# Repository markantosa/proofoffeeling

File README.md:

# Proof of Feeling

**Affective Core AC-7** — a speculative mechatronic artefact: an artificial
robotic heart that makes a humanoid AI's internal state visible through
pulse, motion, and light.

<p align="center">
  
  <br><sub>Render made in Blender.</sub>
</p>

<p align="center">
  
  <br><sub>▶ Short demo — <a href="https://youtu.be/jkcCoCJa7ys">watch on YouTube</a></sub>
</p>

See [`docs/design-reference.md`](docs/design-reference.md) for the full
project concept and design brief.

## Repository Layout

```
.
├── docs/               Project-wide documentation
│   ├── design-reference.md          Project context/story + physical prototype
│   └── pcb-design-reference.md      KiCad 10 PCB design reference
├── firmware/           ESP32-C6-Supermini embedded firmware
│   ├── src/             Servo sweep, LED chase, proximity speed, eye animation, BLE telemetry
│   └── include/          Pin assignments, tunables, BLE UUIDs
├── dashboard/          BLE debug dashboard — ASCII face/sonar/heartbeat, Web Bluetooth (Chrome/Edge only)
├── electronics/        KiCad PCB project (single-layer milled board)
└── mechanical/         3D models — printable STL/3MF tracked via Git LFS; source .blend files not included yet
```

## Hardware Summary

* ESP32-C6-Supermini
* 2x SG92R micro servos, 5V (continuous 0–180° sweep, mirrored) — chosen over MG995 for size
* HC-SR04 ultrasonic sensor (proximity → continuous speed control)
* 1x momentary button, wired but currently unused by firmware
* 8x auxiliary LEDs, top-to-bottom chase ("pulse point" glow array)
* I2C OLED (SSD1306-class), 4-pin header — always-on blinking eye
* BLE telemetry (built-in radio) — feeds the debug dashboard, see below
* Custom single-layer milled PCB (KiCad, `electronics/`)
* Powered via 5V DC barrel plug

## Tools

* 3D modelling — Blender
* PCB design — KiCad
* Firmware — written with the aid of Claude

## Credits

* Heart geometry developed from [Realistic Human Heart](https://sketchfab.com/3d-models/realistic-human-heart-3f8072336ce94d18b3d0d055a1ece089) (Sketchfab)

<table>
  <tr>
    <td align="center"><br><sub>Populated board render</sub></td>
    <td align="center"><br><sub>B.Cu routing</sub></td>
    <td align="center"><br><sub>Desktop CNC isolation milling</sub></td>
  </tr>
</table>

## Build

<table>
  <tr>
    <td align="center"><br><sub>Assembly</sub></td>
    <td align="center"><br><sub>Finished artefact</sub></td>
  </tr>
</table>

## Getting Started

* Project context, story, and what a viewer experiences: [`docs/design-reference.md`](docs/design-reference.md)
* Firmware build/flash instructions: [`firmware/README.md`](firmware/README.md)
* PCB design reference: [`docs/pcb-design-reference.md`](docs/pcb-design-reference.md)
* KiCad project: [`electronics/EPD 3D G6.kicad_pro`](electronics/EPD%203D%20G6.kicad_pro)
* BLE debug dashboard: [`dashboard/index.html`](dashboard/index.html) — open directly in Chrome or Edge (desktop/Android; Web Bluetooth isn't supported in Firefox/Safari), click **Connect**, pick "AC-7"

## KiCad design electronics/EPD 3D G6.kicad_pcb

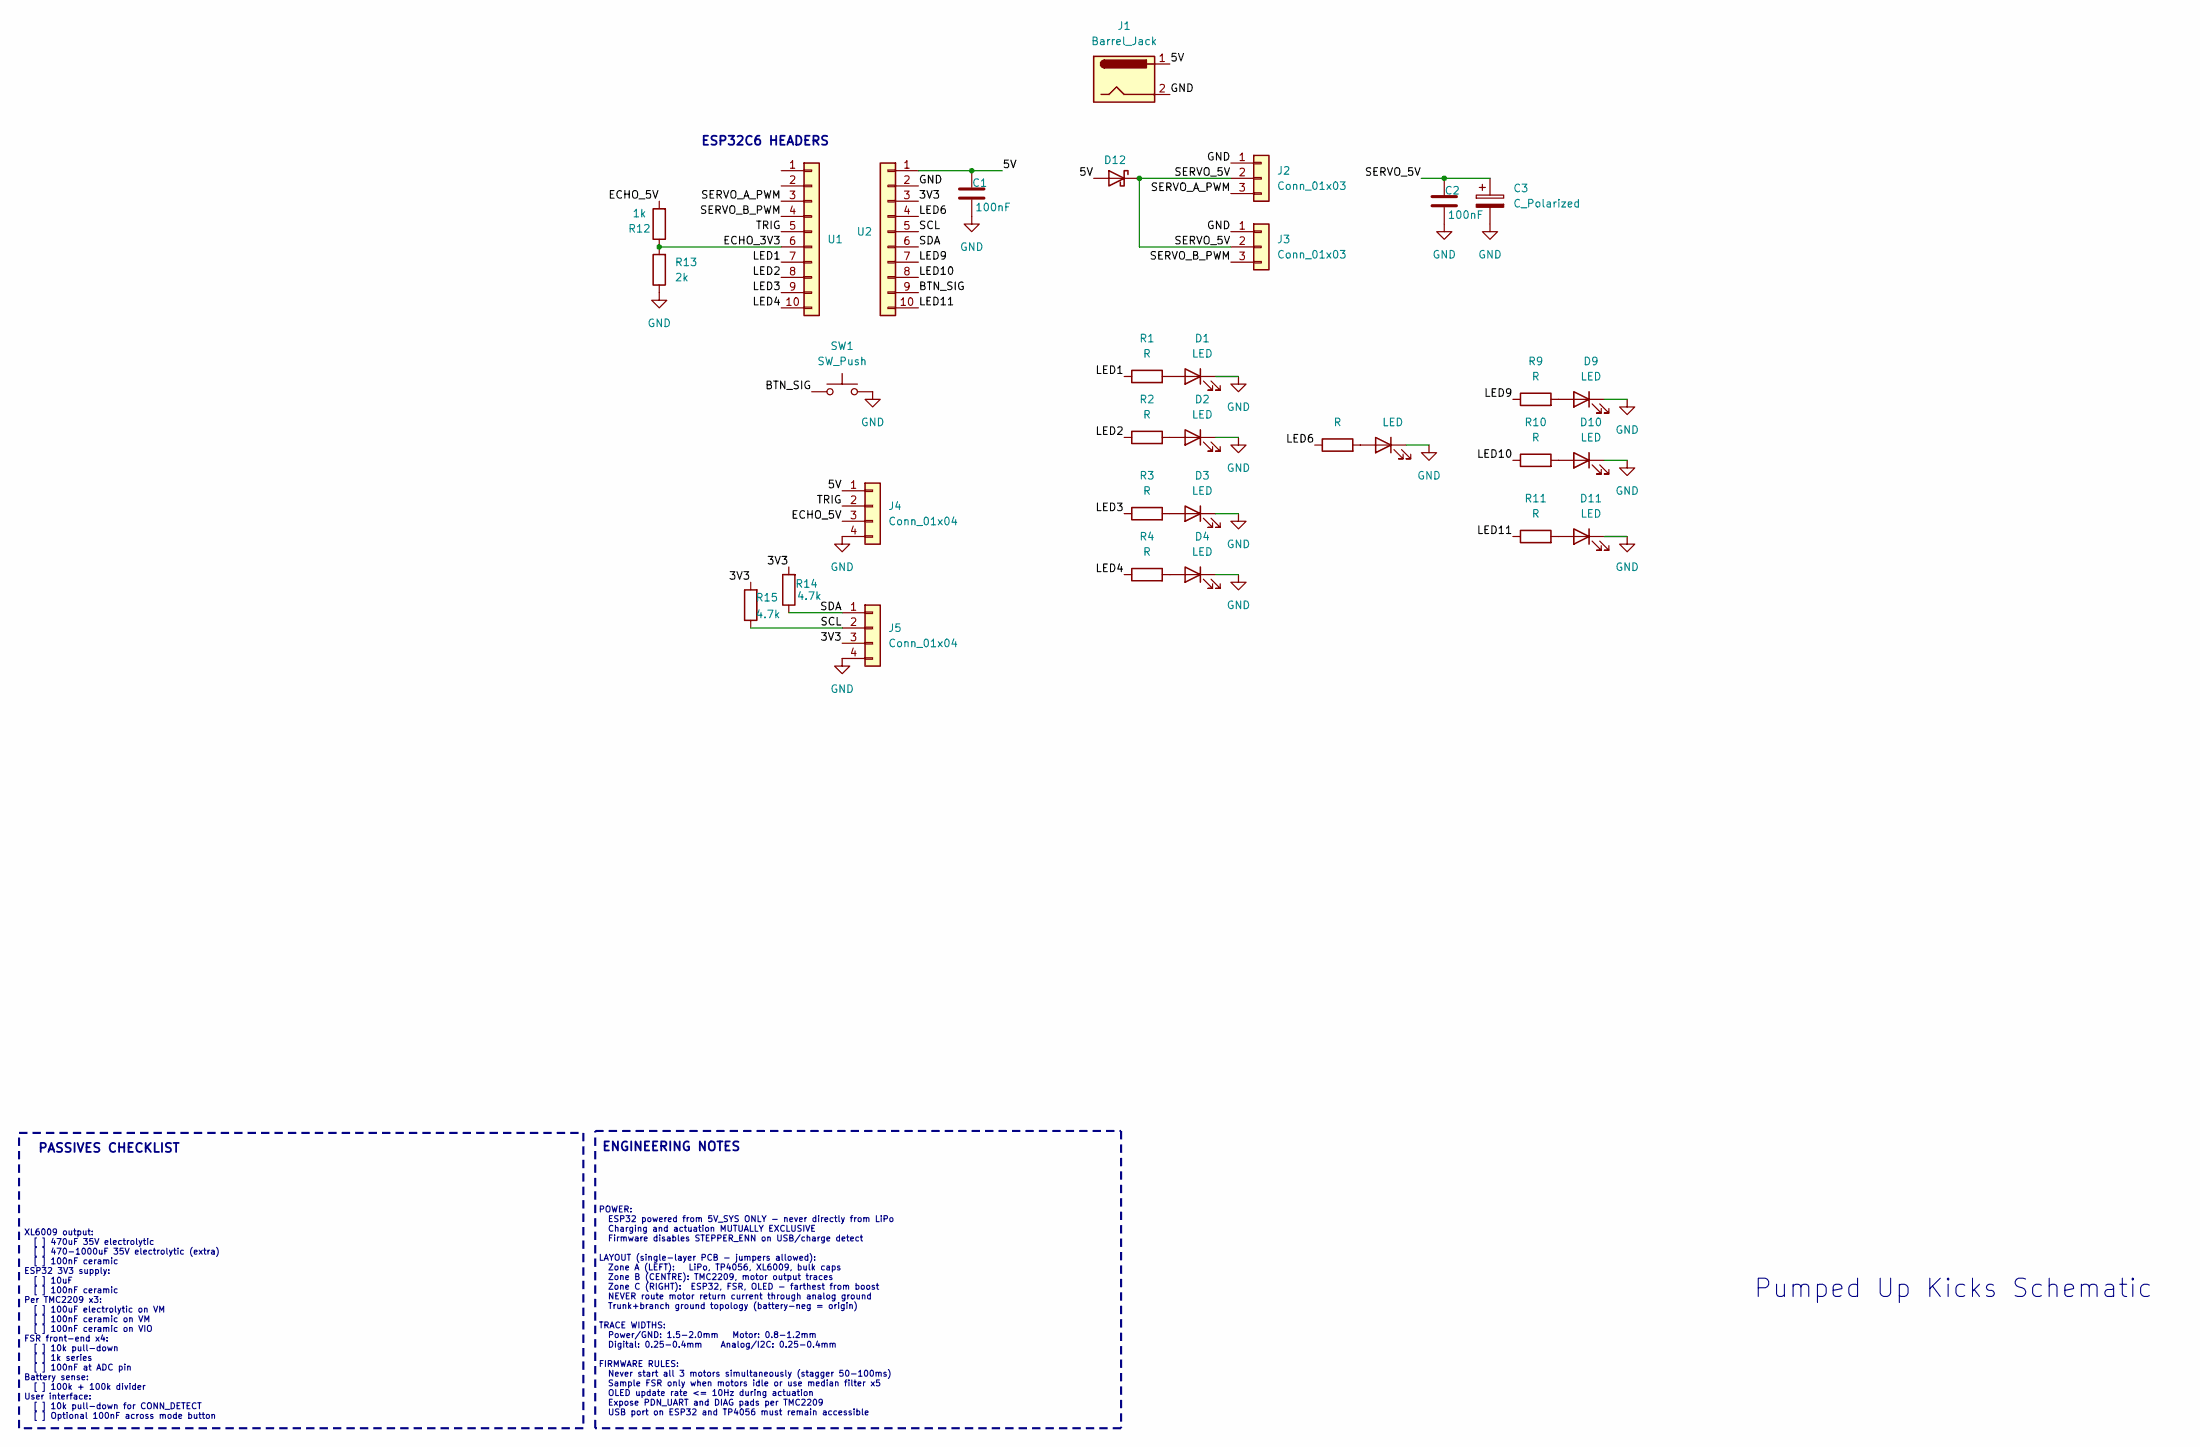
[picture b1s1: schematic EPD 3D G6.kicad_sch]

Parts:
C1, C2: 100nF; C_Disc_D5.0mm_W2.5mm_P5.00mm
C3: C_Polarized; CP_Radial_D8.0mm_P3.50mm
D1, D2, D3, D4, D6, D9, D10, D11: LED; LED_D5.0mm
D12: D_Schottky; D_DO-201AD_P15.24mm_Horizontal
J1: Barrel_Jack; BarrelJack_GCT_DCJ200-10-A_Horizontal
J2, J3: Conn_01x03; PinSocket_1x03_P2.54mm_Vertical
J4, J5: Conn_01x04; PinSocket_1x04_P2.54mm_Vertical
R1, R2, R3, R4, R6, R9, R10, R11: R; R_Axial_DIN0207_L6.3mm_D2.5mm_P7.62mm_Horizontal
R12: 1k; R_Axial_DIN0207_L6.3mm_D2.5mm_P7.62mm_Horizontal
R13: 2k; R_Axial_DIN0207_L6.3mm_D2.5mm_P7.62mm_Horizontal
R14, R15: 4.7k; R_Axial_DIN0207_L6.3mm_D2.5mm_P7.62mm_Horizontal
SW1: SW_Push; SW_PUSH_6mm
U1, U2: Conn_01x10; PinSocket_1x10_P2.54mm_Vertical

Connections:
/3V3: J5.3, R14.2, R15.2, U2.3
/5V: C1.1, D12.2 (A), J1.1, J4.1, U2.1
/BTN_SIG: SW1.1, U2.9
/ECHO_3V3: R12.1, R13.2, U1.6
/ECHO_5V: J4.3, R12.2
/LED1: R1.1, U1.7
/LED2: R2.1, U1.8
/LED3: R3.1, U1.9
/LED4: R4.1, U1.10
/LED6: R6.1, U2.4
/LED9: R9.1, U2.7
/LED10: R10.1, U2.8
/LED11: R11.1, U2.10
/SCL: J5.2, R15.1, U2.5
/SDA: J5.1, R14.1, U2.6
/SERVO_5V: C2.1, C3.1, D12.1 (K), J2.2, J3.2
/SERVO_A_PWM: J2.3, U1.3
/SERVO_B_PWM: J3.3, U1.4
/TRIG: J4.2, U1.5
GND: C1.2, C2.2, C3.2, D1.1 (K), D2.1 (K), D3.1 (K), D4.1 (K), D6.1 (K), D9.1 (K), D10.1 (K), D11.1 (K), J1.2, J2.1, J3.1, J4.4, J5.4, R13.1, SW1.2, U2.2
unnamed: D1.2 (A), R1.2
unnamed: D2.2 (A), R2.2
unnamed: D3.2 (A), R3.2
unnamed: D4.2 (A), R4.2
unnamed: D6.2 (A), R6.2
unnamed: D9.2 (A), R9.2
unnamed: D10.2 (A), R10.2
unnamed: D11.2 (A), R11.2

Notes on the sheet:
Pumped Up Kicks Schematic
PASSIVES CHECKLIST
ESP32C6 HEADERS
XL6009 output: [ ] 470uF 35V electrolytic [ ] 470-1000uF 35V electrolytic (extra) [ ] 100nF ceramic ESP32 3V3 supply: [ ] 10uF [ ] 100nF ceramic Per TMC2209 x3: [ ] 100uF electrolytic on VM [ ] 100nF ceramic on VM [ ] 100nF ceramic on VIO FSR front-end x4: [ ] 10k pull-down [ ] 1k series [ ] 100nF 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
POWER: ESP32 powered from 5V_SYS ONLY - never directly from LiPo Charging and actuation MUTUALLY EXCLUSIVE Firmware disables STEPPER_ENN on USB/charge detect LAYOUT (single-layer PCB - jumpers allowed): Zone A (LEFT): LiPo, TP4056, XL6009, bulk caps Zone B (CENTRE): TMC2209, motor output traces Zon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
ENGINEERING NOTES

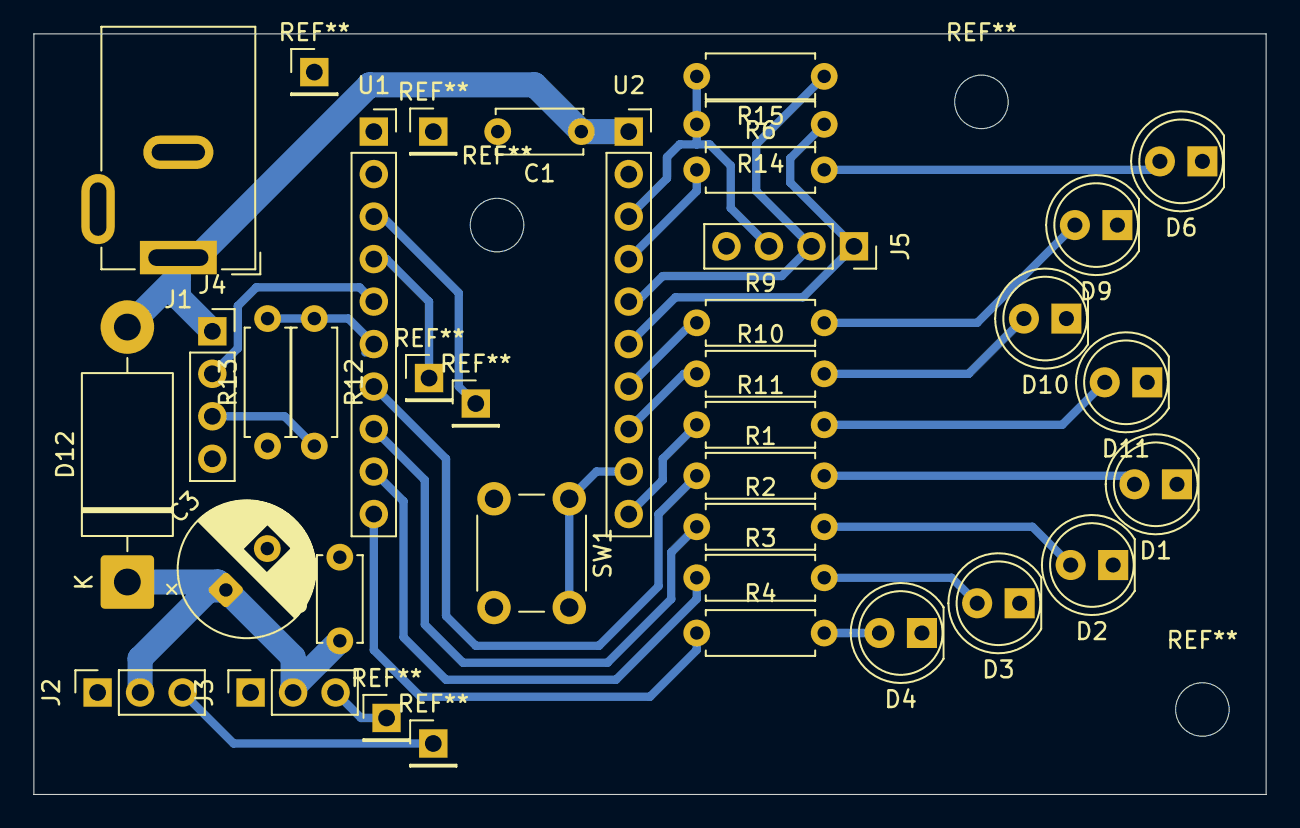
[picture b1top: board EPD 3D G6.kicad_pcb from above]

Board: 2 copper layers, 73.7 x 45.5 mm, 32 parts (0 on the bottom side), 28 nets.
